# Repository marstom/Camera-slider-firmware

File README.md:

# Camera-slider-firmware
Stepper motor controller firmware for camera slider, MCU: AtMega32. This software is using to controll 1-axis camera slider using stepper motor. It is designed to work with Cannon photo cameras. Camera must be in Bulb mode, device controll camera shutter. Stepper motor is slow, this device is designed for long timelapses.
### Features:
* Show settings on lcd display,
* Timelapse photos with slide effect,
* User can set timelapse length in hours.

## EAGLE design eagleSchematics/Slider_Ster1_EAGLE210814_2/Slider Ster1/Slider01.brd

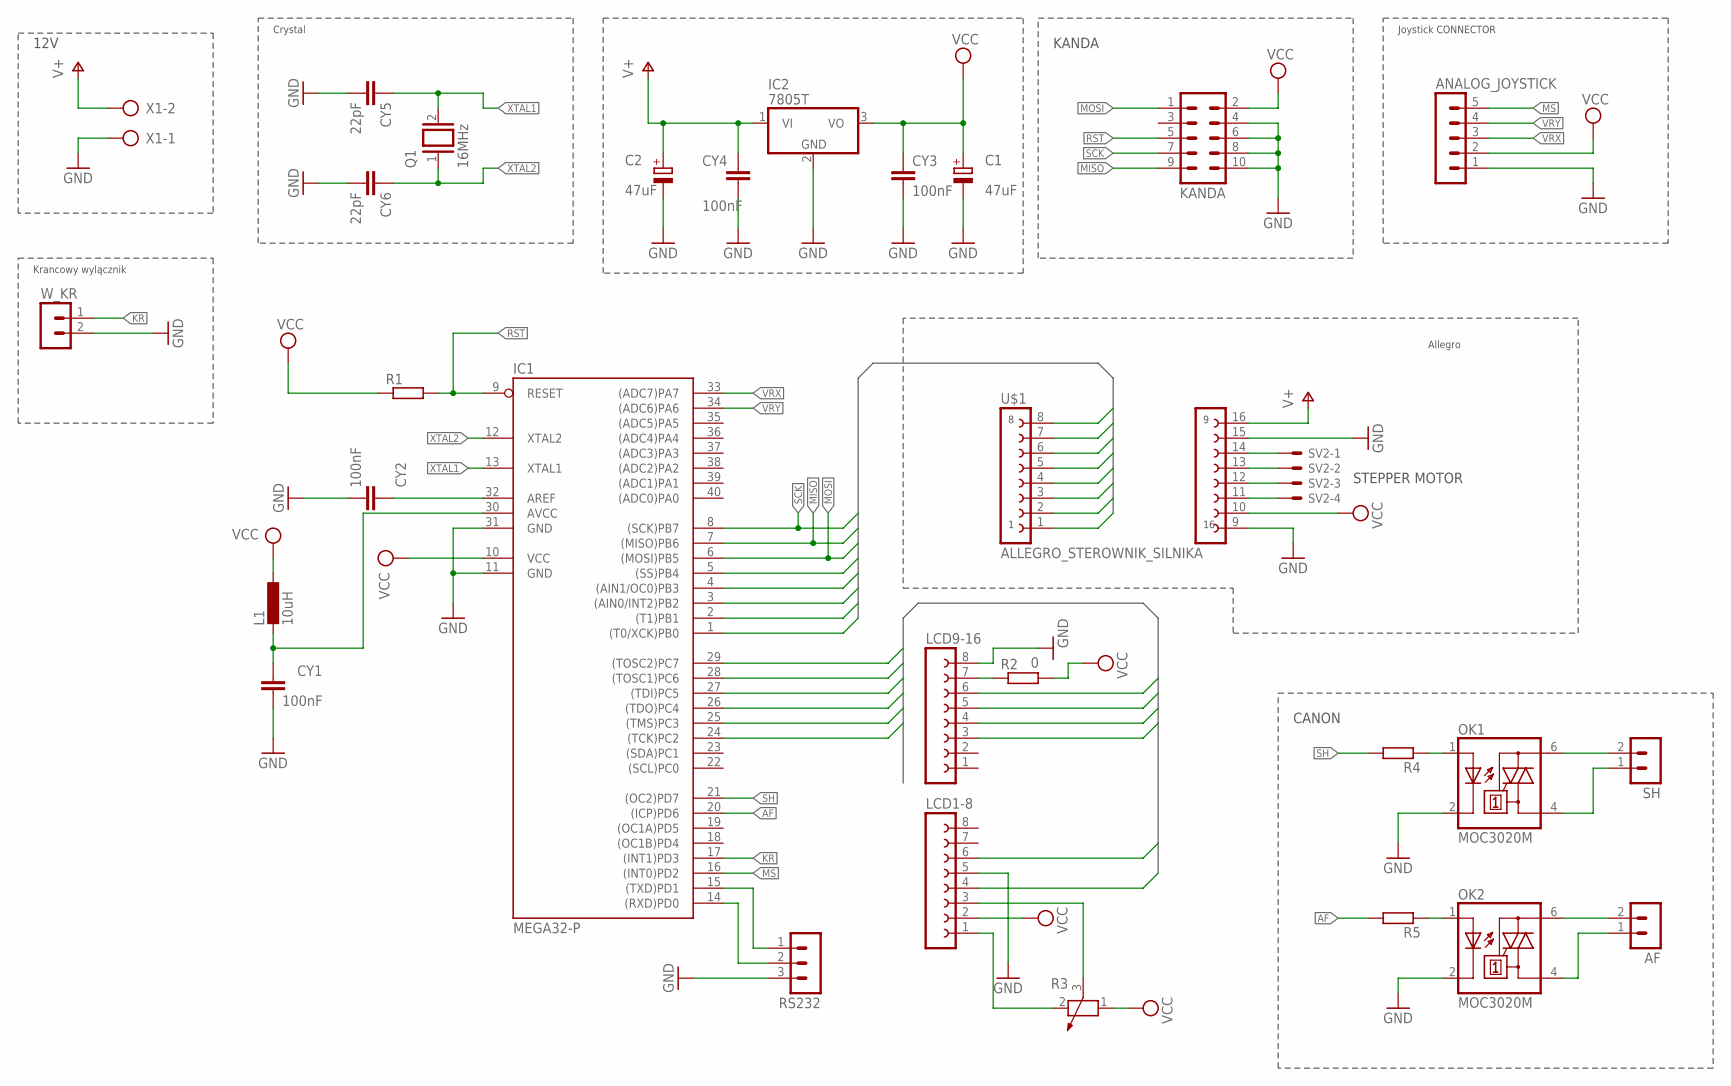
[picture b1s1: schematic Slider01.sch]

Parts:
AF: LSTB2
ANALOG_JOYSTICK: MA05-1
C1, C2: 47uF; E5-6
CY1, CY2, CY3, CY4: 100nF; C050-024X044
CY5, CY6: 22pF; C1206
IC1: MEGA32-P; DIL40
IC2: 7805T; TO220H
KANDA: MA05-2
L1: 10uH; 0207/10
LCD1-8, LCD9-16: FE08-1; FE08
OK1, OK2: MOC3020M; DIL06
Q1: 16MHz; QS
R1, R4, R5: R-EU_0207/7; 0207/7
R2: 0; 0207/12
R3: POTENTIOMETER_PT-10; PT-10
RS232: MA03-1
SH: LSTB2
SV2: KK-156-4
U$1: ALLEGRO_STEROWNIK_SILNIKA; ALLEGRO_STEROWNIK
W_KR: LSTB2
X1: AK500/2

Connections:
#E: IC1.25 ((TMS)PC3), LCD1-8.6
AF: IC1.20 ((ICP)PD6), R5.2
D4: IC1.26 ((TDO)PC4), LCD9-16.3
D5: IC1.27 ((TDI)PC5), LCD9-16.4
D6: IC1.28 ((TOSC1)PC6), LCD9-16.5
D7: IC1.29 ((TOSC2)PC7), LCD9-16.6
GND: ANALOG_JOYSTICK.1, C1.-, C2.-, CY1.2, CY2.2, CY3.2, CY4.2, CY5.2, CY6.2, IC1.11 (GND), IC1.31 (GND), IC2.2 (GND), KANDA.4, KANDA.6, KANDA.8, KANDA.10, LCD1-8.5, LCD9-16.8, OK1.2 (C), OK2.2 (C), RS232.3, U$1.9 (A16), U$1.15 (A10), W_KR.2, X1.1
KR: IC1.17 ((INT1)PD3), W_KR.1
MISO: IC1.7 ((MISO)PB6), KANDA.9, U$1.7
MOSI: IC1.6 ((MOSI)PB5), KANDA.1, U$1.6
MS: ANALOG_JOYSTICK.5, IC1.16 ((INT0)PD2)
unnamed: SV2.1, U$1.14 (A11)
unnamed: SV2.2, U$1.13 (A12)
unnamed: SV2.3, U$1.12 (A13)
unnamed: SV2.4, U$1.11 (A14)
unnamed: LCD9-16.7, R2.1
unnamed: CY2.1, IC1.32 (AREF)
unnamed: CY1.1, IC1.30 (AVCC), L1.2
unnamed: LCD1-8.1, R3.2
unnamed: LCD1-8.3, R3.3
unnamed: OK1.1 (A), R4.1
unnamed: OK2.1 (A), R5.1
unnamed: OK1.6 (A2), SH.2
unnamed: OK1.4 (A1), SH.1
unnamed: AF.2, OK2.6 (A2)
unnamed: AF.1, OK2.4 (A1)
unnamed: IC1.15 ((TXD)PD1), RS232.1
unnamed: IC1.14 ((RXD)PD0), RS232.2
PB0: IC1.1 ((T0/XCK)PB0), U$1.1
PB1: IC1.2 ((T1)PB1), U$1.2
PB2: IC1.3 ((AIN0/INT2)PB2), U$1.3
PB3: IC1.4 ((AIN1/OC0)PB3), U$1.4
PB4: IC1.5 ((SS)PB4), U$1.5
RS: IC1.24 ((TCK)PC2), LCD1-8.4
RST: IC1.9 (RESET), KANDA.5, R1.2
SCK: IC1.8 ((SCK)PB7), KANDA.7, U$1.8
SH: IC1.21 ((OC2)PD7), R4.2
V+: C2.+, CY4.1, IC2.1 (VI), U$1.16 (A9), X1.2
VCC: ANALOG_JOYSTICK.2, C1.+, CY3.1, IC1.10 (VCC), IC2.3 (VO), KANDA.2, L1.1, LCD1-8.2, R1.1, R2.2, R3.1, U$1.10 (A15)
VRX: ANALOG_JOYSTICK.3, IC1.33 ((ADC7)PA7)
VRY: ANALOG_JOYSTICK.4, IC1.34 ((ADC6)PA6)
XTAL1: CY5.1, IC1.13 (XTAL1), Q1.2
XTAL2: CY6.1, IC1.12 (XTAL2), Q1.1

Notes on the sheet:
KANDA
STEPPER MOTOR
Joystick CONNECTOR
Crystal
Allegro
CANON
Krancowy wylącznik
12V

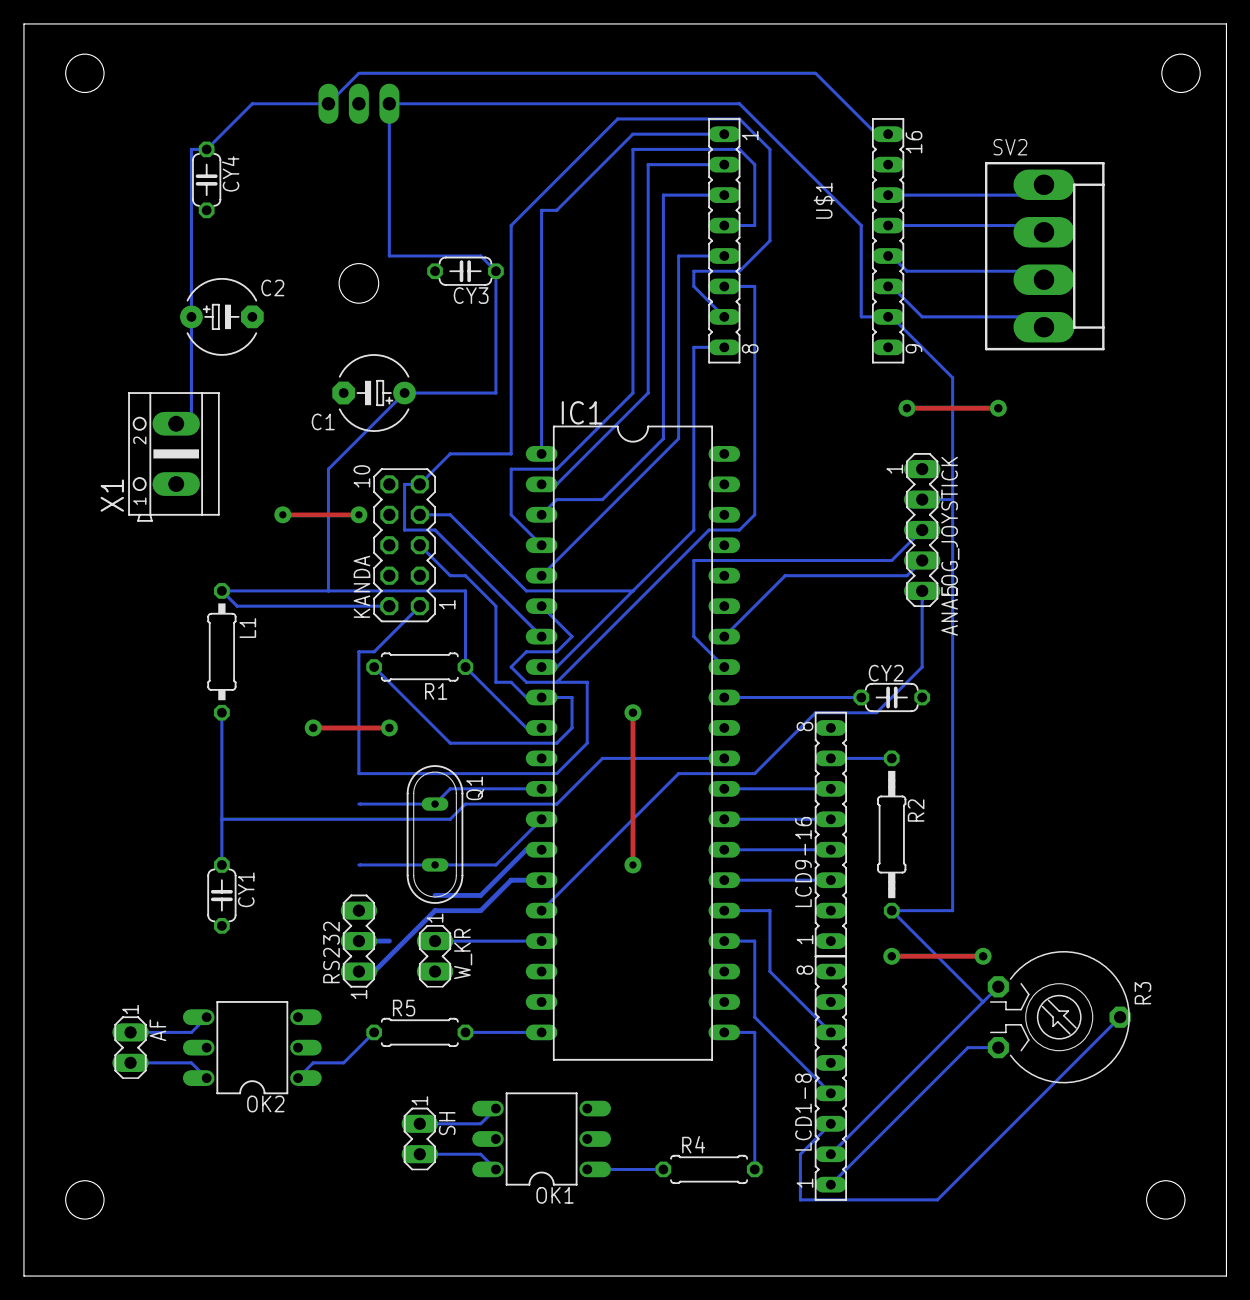
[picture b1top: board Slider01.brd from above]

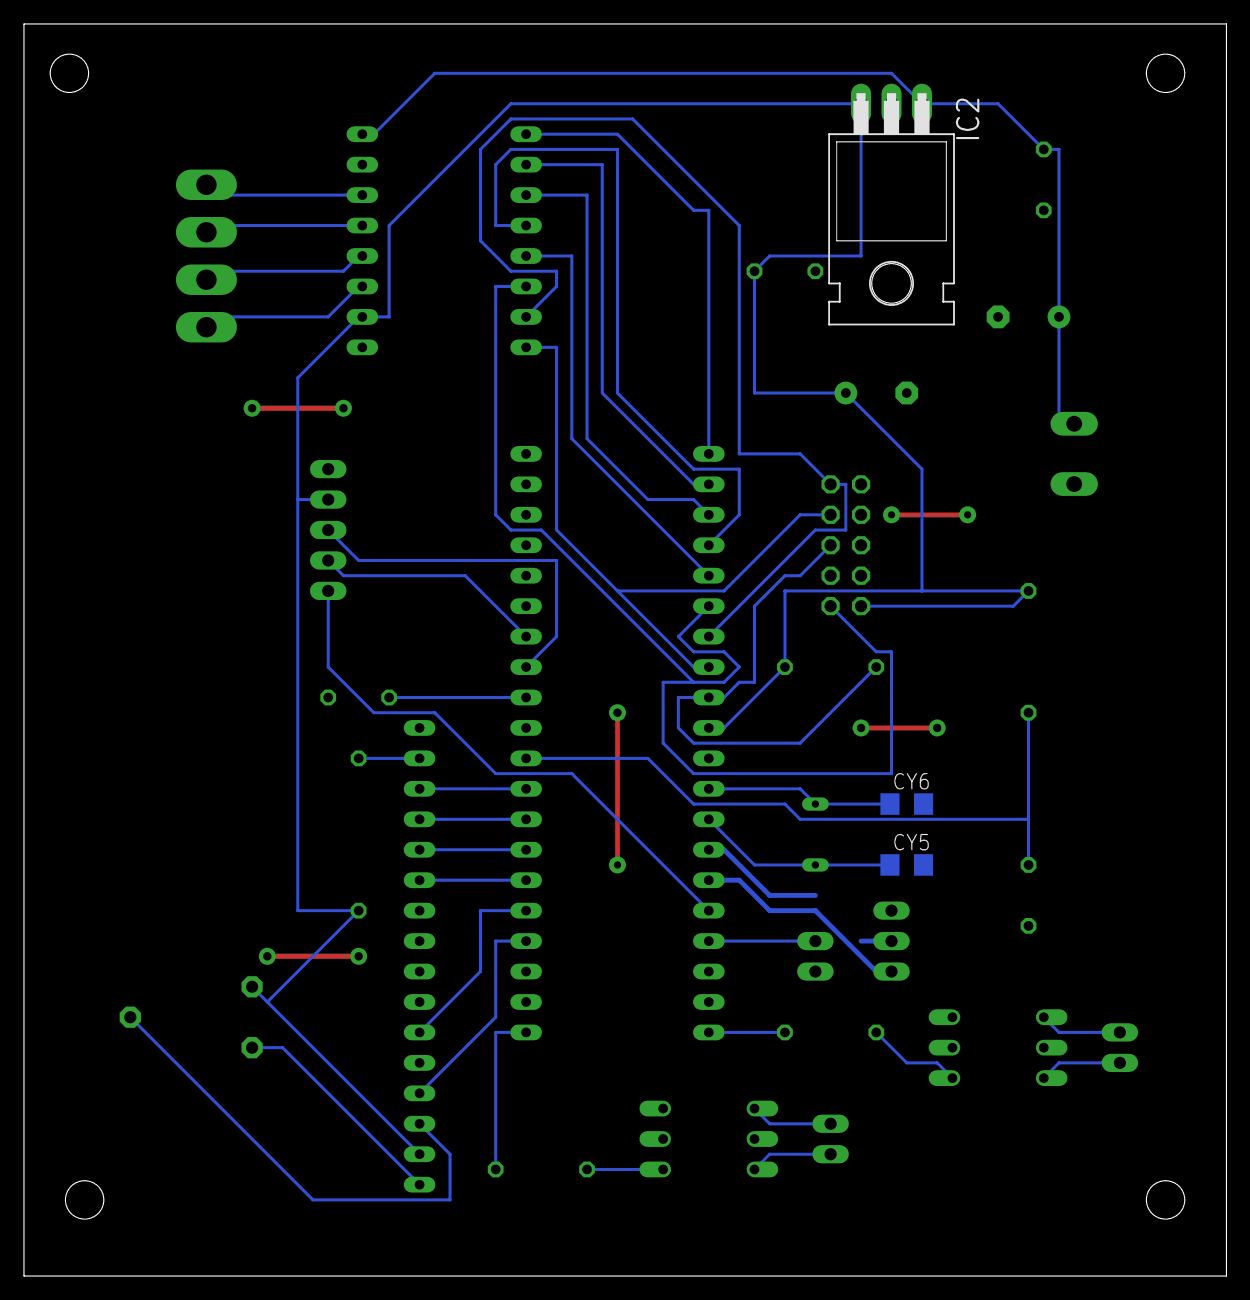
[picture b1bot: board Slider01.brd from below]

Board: 2 copper layers, 100.3 x 104.4 mm, 30 parts (3 on the bottom side), 43 nets.

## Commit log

2016-05-18 Camera slider firmware v0.13
2017-05-28 Add schematics and board design PCB
